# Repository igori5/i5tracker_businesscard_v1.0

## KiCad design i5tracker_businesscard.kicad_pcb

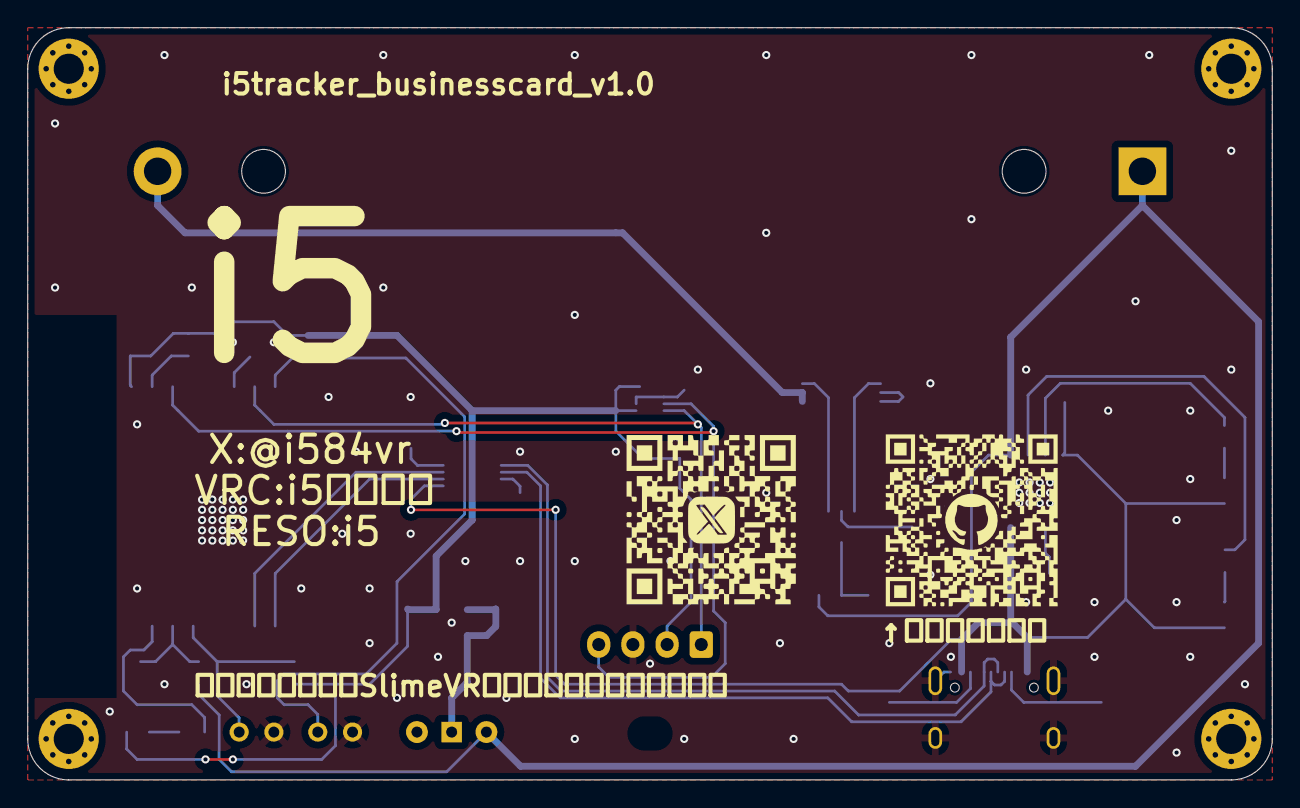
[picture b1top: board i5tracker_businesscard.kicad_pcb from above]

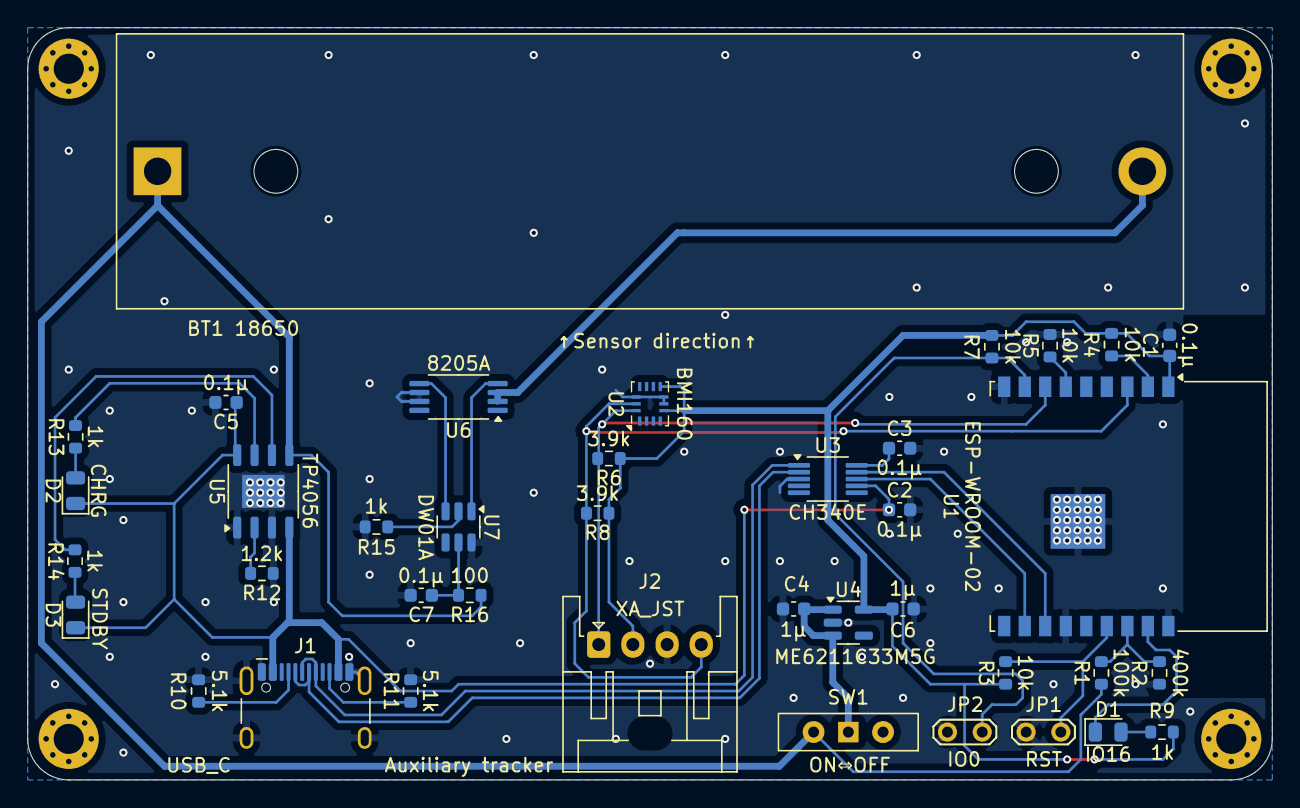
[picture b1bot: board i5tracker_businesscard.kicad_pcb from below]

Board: 2 copper layers, 91.0 x 55.0 mm, 39 parts (39 on the bottom side), 31 nets.

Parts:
BT1: 18650; BatteryHolder_MPD_BH-18650-PC2
C1, C2, C3, C5, C7: 0.1μ; C_0603_1608Metric
C4, C6: 1μ; C_0603_1608Metric
D1: IO16; LED_0805_2012Metric
D2: CHRG; LED_0805_2012Metric
D3: STDBY; LED_0805_2012Metric
J1: USB_C; USB_C_Receptacle_HCTL_HC-TYPE-C-16P-01A
J2: XA_JST; JST_XA_S04B-XASK-1_1x04_P2.50mm_Horizontal
JP1: RST; TestPoint_2Pads_Pitch2.54mm_Drill0.8mm
JP2: IO0; TestPoint_2Pads_Pitch2.54mm_Drill0.8mm
R1: 100k; R_0603_1608Metric
R2: 400k; R_0603_1608Metric
R3, R4, R5, R7: 10k; R_0603_1608Metric
R6, R8: 3.9k; R_0603_1608Metric
R9, R13, R14, R15: 1k; R_0603_1608Metric
R10, R11: 5.1k; R_0603_1608Metric
R12: 1.2k; R_0603_1608Metric
R16: 100; R_0603_1608Metric
SW1: SW_SPDT; SW_Slide-03_Wuerth-WS-SLTV_10x2.5x6.4_P2.54mm
U1: ESP-WROOM-02
U2: BMI160; Bosch_LGA-14_3x2.5mm_P0.5mm
U3: CH340E; MSOP-10_3x3mm_P0.5mm
U4: ME6211C33M5G; SOT-23-5
U5: TP4056; HSOP-8-1EP_3.9x4.9mm_P1.27mm_EP2.41x3.1mm
U6: 8205A; TSSOP-8_4.4x3mm_P0.65mm
U7: DW01A; SOT-23-6

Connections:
+3.3V: C1.1, C6.1, J2.2, R3.1, R4.1, R6.1, R7.1, R8.1, R9.1, U1.1 (VDD), U2.5 (VDDIO), U2.8 (VDD), U4.5 (VOUT)
+5V: C2.1, C5.1, D2.1 (K), D3.1 (K), J1.A4 (VBUS), J1.A9 (VBUS), J1.B4 (VBUS), J1.B9 (VBUS), U3.7 (VCC), U5.4 (Vcc), U5.8 (CE)
+BATT: BT1.1 (+), R1.1, R16.1, SW1.2 (B), U5.5 (BAT)
-BATT: BT1.2 (-), U6.2 (S1), U6.3 (S1)
/BATT: C4.1, SW1.1 (A), U4.1 (VIN), U4.3 (EN)
/D+: J1.A6 (D+), J1.B6 (D+), U3.1 (UD+)
/D-: J1.A7 (D-), J1.B7 (D-), U3.2 (UD-)
/RXD: U1.11 (RXD), U3.8 (TXD)
/SCL: J2.4, R8.2, U1.3 (IO14), U2.13 (SCx)
/SDA: J2.1, R6.2, U1.7 (IO2), U2.14 (SDx)
/TXD: U1.12 (TXD), U3.9 (RXD)
GND: C1.2, C2.2, C3.2, C4.2, C5.2, C6.2, C7.2, J1.A1 (GND), J1.A12 (GND), J1.B1 (GND), J1.B12 (GND), J1.S1 (SHIELD), J2.3, JP1.1 (A), JP2.1 (A), R2.2, R5.2, R10.2, R11.2, R12.1, R15.1, U1.9 (GND), U1.13 (GND), U1.18 (GND), U1.19 (GND), U2.6 (GNDIO), U2.7 (GND), U2.12 (CSB), U3.3 (GND), U4.2 (GND), U5.1 (TEMP), U5.3 (GND), U5.9 (EP), U6.6 (S2), U6.7 (S2), U7.6 (GND)
unnamed: D1.2 (A), R9.2
unnamed: D1.1 (K), U1.17 (IO16)
unnamed: D2.2 (A), R13.1
unnamed: D3.2 (A), R14.1
unnamed: J1.A5 (CC1), R10.1
unnamed: J1.B5 (CC2), R11.1
unnamed: JP1.2 (B), R3.2, U1.15 (RST)
unnamed: JP2.2 (B), R7.2, U1.8 (IO0)
unnamed: R4.2, U1.2 (EN)
unnamed: R5.1, U1.6 (IO15)
unnamed: R1.2, R2.1, U1.16 (TOUT)
unnamed: C3.1, U3.10 (V3)
unnamed: R13.2, U5.7 (CHRG)
unnamed: R12.2, U5.2 (PROG)
unnamed: R14.2, U5.6 (STDBY)
unnamed: U6.4 (G1), U7.1 (OD)
unnamed: U6.5 (G2), U7.3 (OC)
unnamed: R15.2, U7.2 (CS)
unnamed: C7.1, R16.2, U7.5 (VCC)
